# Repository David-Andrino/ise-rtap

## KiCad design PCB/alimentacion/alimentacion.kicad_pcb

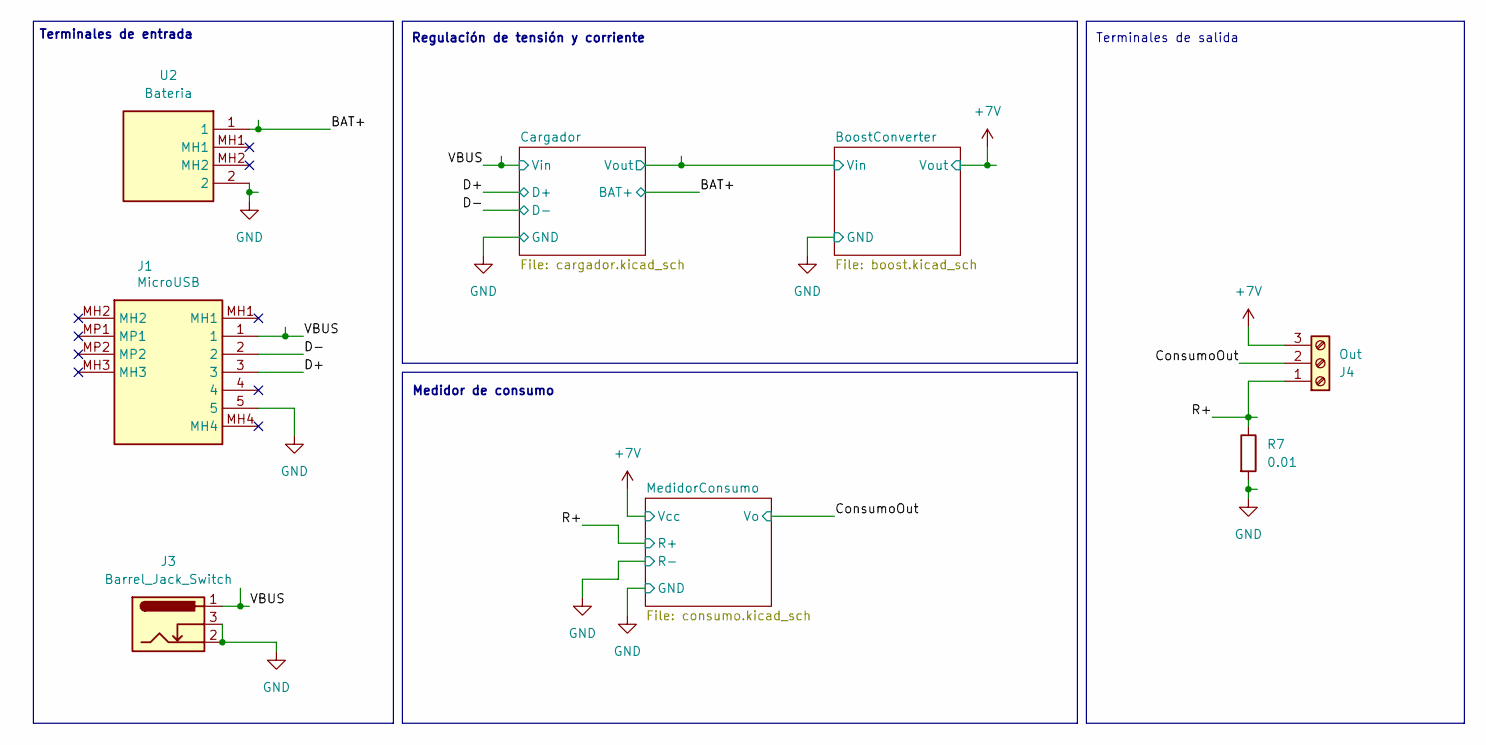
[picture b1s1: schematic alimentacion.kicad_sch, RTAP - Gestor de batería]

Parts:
J1: MicroUSB; 101181940001LF; Manufacturer_Part_Number 10118194-0001LF
J3: Barrel_Jack_Switch; PJ202AH
J4: Out; TerminalBlock_bornier-3_P5.08mm
R7: 0.01; R_1206_3216Metric
U2: Bateria; 12BHC186P1GR; Mouser Part Number 12BHC186P1-GR

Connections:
+7V: J4.3; also elsewhere on the board
/BAT+: U2.1; also elsewhere on the board
/ConsumoOut: J4.2; also elsewhere on the board
/D+: J1.3; also elsewhere on the board
/D-: J1.2; also elsewhere on the board
/R+: J4.1, R7.1; also elsewhere on the board
/VBUS: J1.1, J3.1; also elsewhere on the board
GND: J1.5, J3.2, J3.3, R7.2, U2.2; also elsewhere on the board

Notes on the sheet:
Terminales de salida
Medidor de consumo
Terminales de entrada
Regulación de tensión y corriente

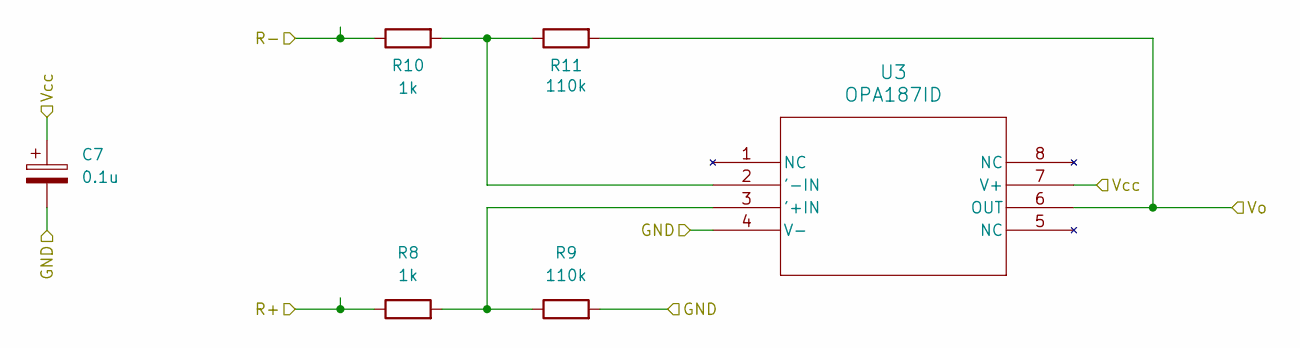
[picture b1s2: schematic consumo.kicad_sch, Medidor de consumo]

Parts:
C7: 0.1u; C_0603_1608Metric
R8, R10: 1k; R_0603_1608Metric
R9, R11: 110k; R_0603_1608Metric
U3: OPA187ID; D8_TEX-M

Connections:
+7V: C7.1, U3.7 (V+); also elsewhere on the board
/ConsumoOut: R11.2, U3.6 (OUT); also elsewhere on the board
/R+: R8.1; also elsewhere on the board
GND: C7.2, R9.2, R10.1, U3.4 (V-); also elsewhere on the board
unnamed: R8.2, R9.1, U3.3 ('+IN)
unnamed: R10.2, R11.1, U3.2 ('-IN)

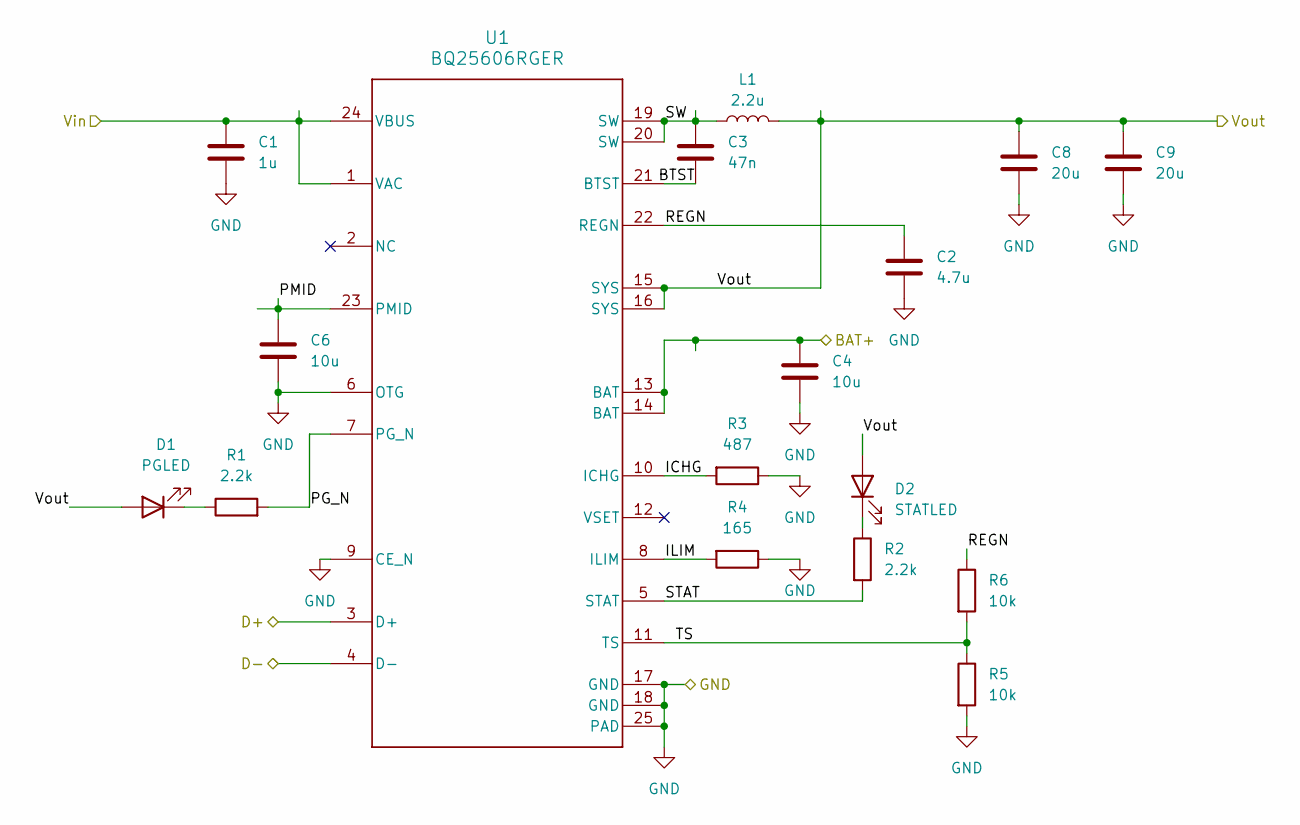
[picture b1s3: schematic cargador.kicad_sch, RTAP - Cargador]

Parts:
C1: 1u; C_0603_1608Metric
C2: 4.7u; C_0603_1608Metric
C3: 47n; C_0603_1608Metric
C4, C6: 10u; C_0603_1608Metric
C8, C9: 20u; C_0603_1608Metric
D1: PGLED; D_0603_1608Metric_Pad1.05x0.95mm_HandSolder
D2: STATLED; D_0603_1608Metric_Pad1.05x0.95mm_HandSolder
L1: 2.2u; SRN6045
R1, R2: 2.2k; R_0603_1608Metric
R3: 487; R_0603_1608Metric
R4: 165; R_0603_1608Metric
R5, R6: 10k; R_0603_1608Metric
U1: BQ25606RGER; RGE0024H_NV

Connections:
/BAT+: C4.2, U1.13 (BAT), U1.14 (BAT); also elsewhere on the board
/BoostConverter/Vin: C8.2, C9.2, D1.2 (A), D2.2 (A), L1.2, U1.15 (SYS), U1.16 (SYS); also elsewhere on the board
/Cargador/BTST: C3.2, U1.21 (BTST)
/Cargador/ICHG: R3.2, U1.10 (ICHG)
/Cargador/ILIM: R4.2, U1.8 (ILIM)
/Cargador/PG_N: R1.2, U1.7 (PG_N)
/Cargador/PMID: C6.1, U1.23 (PMID)
/Cargador/REGN: C2.2, R6.1, U1.22 (REGN)
/Cargador/STAT: R2.2, U1.5 (STAT)
/Cargador/SW: C3.1, L1.1, U1.19 (SW), U1.20 (SW)
/Cargador/TS: R5.1, R6.2, U1.11 (TS)
/D+: U1.3 (D+); also elsewhere on the board
/D-: U1.4 (D-); also elsewhere on the board
/VBUS: C1.1, U1.1 (VAC), U1.24 (VBUS); also elsewhere on the board
GND: C1.2, C2.1, C4.1, C6.2, C8.1, C9.1, R3.1, R4.1, R5.2, U1.6 (OTG), U1.9 (CE_N), U1.17 (GND), U1.18 (GND), U1.25 (PAD); also elsewhere on the board
unnamed: D1.1 (K), R1.1
unnamed: D2.1 (K), R2.1

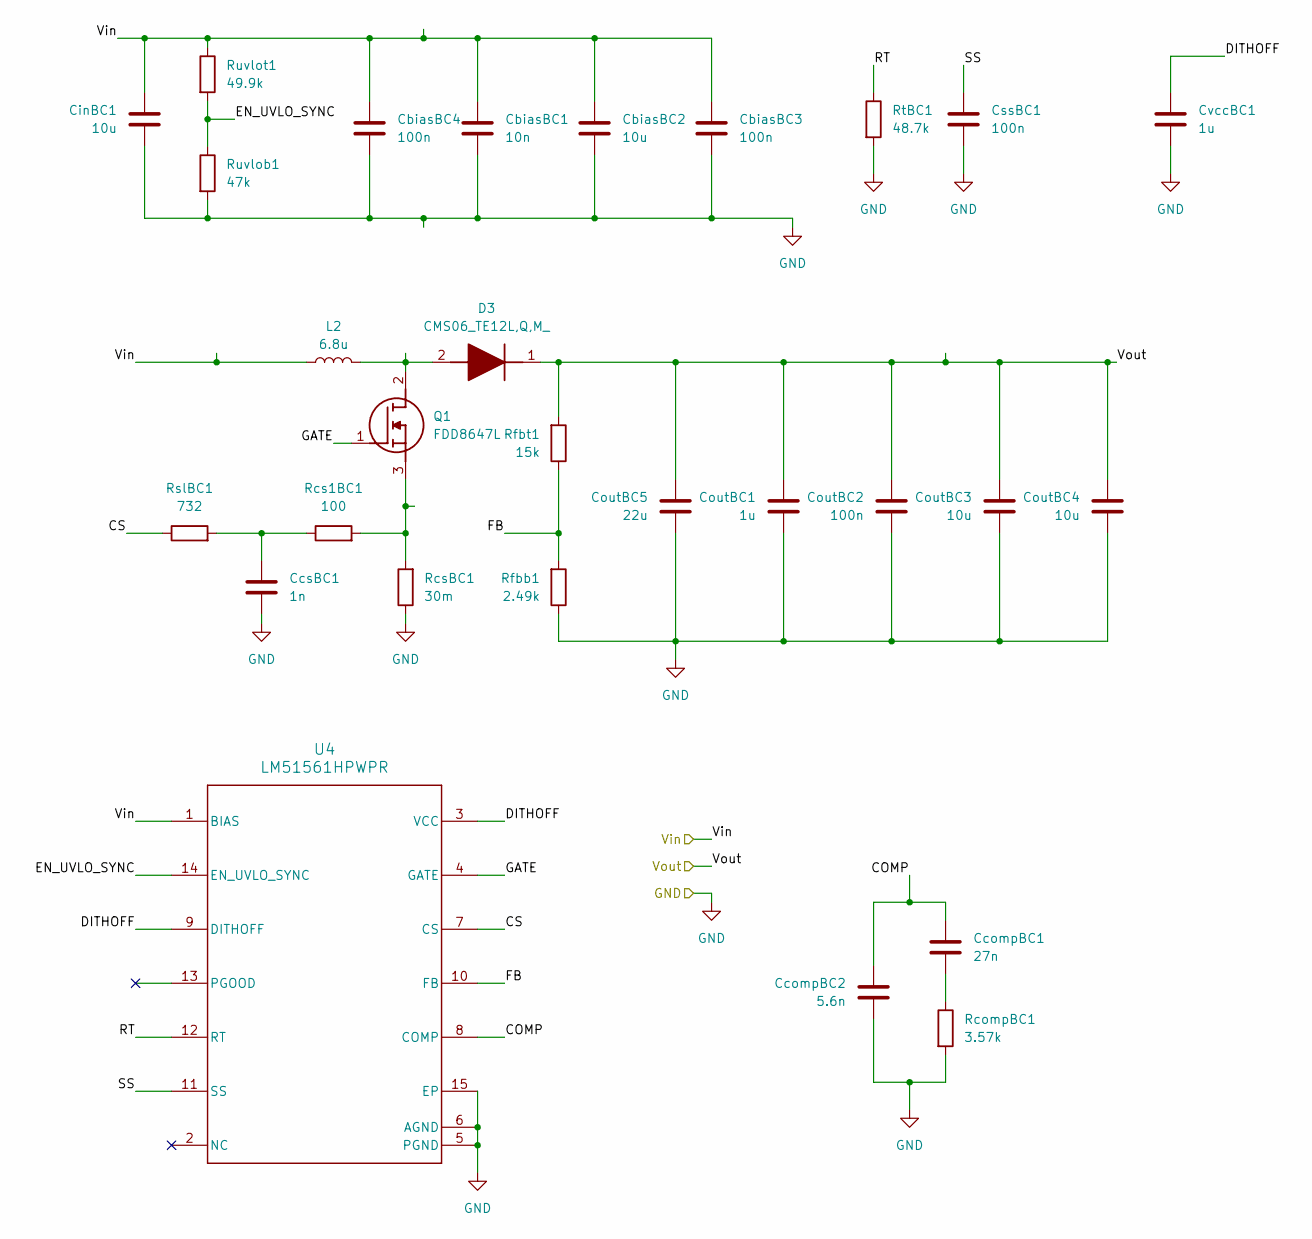
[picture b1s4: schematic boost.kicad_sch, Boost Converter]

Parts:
CbiasBC1: 10n; C_1206_3216Metric_Pad1.33x1.80mm_HandSolder
CbiasBC2: 10u; C_1206_3216Metric_Pad1.33x1.80mm_HandSolder
CbiasBC3, CbiasBC4: 100n; C_1206_3216Metric_Pad1.33x1.80mm_HandSolder
CcompBC1: 27n; C_0603_1608Metric
CcompBC2: 5.6n; C_0603_1608Metric
CcsBC1: 1n; C_0603_1608Metric
CinBC1: 10u; C_1206_3216Metric_Pad1.33x1.80mm_HandSolder
CoutBC1: 1u; C_1206_3216Metric_Pad1.33x1.80mm_HandSolder
CoutBC2: 100n; C_1206_3216Metric_Pad1.33x1.80mm_HandSolder
CoutBC3, CoutBC4: 10u; C_1206_3216Metric_Pad1.33x1.80mm_HandSolder
CoutBC5: 22u; C_1206_3216Metric_Pad1.33x1.80mm_HandSolder
CssBC1: 100n; C_0603_1608Metric
CvccBC1: 1u; C_0603_1608Metric
D3: CMS06_TE12L,Q,M_; SODFL4724X108N; Mouser Part Number 757-CMS06TE12L,Q,M
L2: 6.8u; SRN6045
Q1: FDD8647L; Mouser Part Number 512-FDD8647L
RcompBC1: 3.57k; R_0603_1608Metric
Rcs1BC1: 100; R_0603_1608Metric
RcsBC1: 30m; R_1206_3216Metric
Rfbb1: 2.49k; R_0603_1608Metric
Rfbt1: 15k; R_0603_1608Metric
RslBC1: 732; R_0603_1608Metric
RtBC1: 48.7k; R_0603_1608Metric
Ruvlob1: 47k; R_0603_1608Metric
Ruvlot1: 49.9k; R_0603_1608Metric
U4: LM51561HPWPR; PWP0014H-IPC_A

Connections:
+7V: CoutBC1.2, CoutBC2.2, CoutBC3.2, CoutBC4.2, CoutBC5.2, D3.1 (K), Rfbt1.2; also elsewhere on the board
/BoostConverter/COMP: CcompBC1.2, CcompBC2.2, U4.8 (COMP)
/BoostConverter/CS: RslBC1.1, U4.7 (CS)
/BoostConverter/DITHOFF: CvccBC1.2, U4.3 (VCC), U4.9 (DITHOFF)
/BoostConverter/EN_UVLO_SYNC: Ruvlob1.1, Ruvlot1.2, U4.14 (EN_UVLO_SYNC)
/BoostConverter/FB: Rfbb1.2, Rfbt1.1, U4.10 (FB)
/BoostConverter/GATE: Q1.1 (G), U4.4 (GATE)
/BoostConverter/RT: RtBC1.1, U4.12 (RT)
/BoostConverter/SS: CssBC1.2, U4.11 (SS)
/BoostConverter/Vin: CbiasBC1.2, CbiasBC2.2, CbiasBC3.2, CbiasBC4.2, CinBC1.1, L2.1, Ruvlot1.1, U4.1 (BIAS); also elsewhere on the board
GND: CbiasBC1.1, CbiasBC2.1, CbiasBC3.1, CbiasBC4.1, CcompBC2.1, CcsBC1.1, CinBC1.2, CoutBC1.1, CoutBC2.1, CoutBC3.1, CoutBC4.1, CoutBC5.1, CssBC1.1, CvccBC1.1, RcompBC1.2, RcsBC1.1, Rfbb1.1, RtBC1.2, Ruvlob1.2, U4.5 (PGND), U4.6 (AGND), U4.15 (EP); also elsewhere on the board
unnamed: CcompBC1.1, RcompBC1.1
unnamed: CcsBC1.2, Rcs1BC1.1, RslBC1.2
unnamed: D3.2 (A), L2.2, Q1.2 (D)
unnamed: Q1.3 (S), Rcs1BC1.2, RcsBC1.2

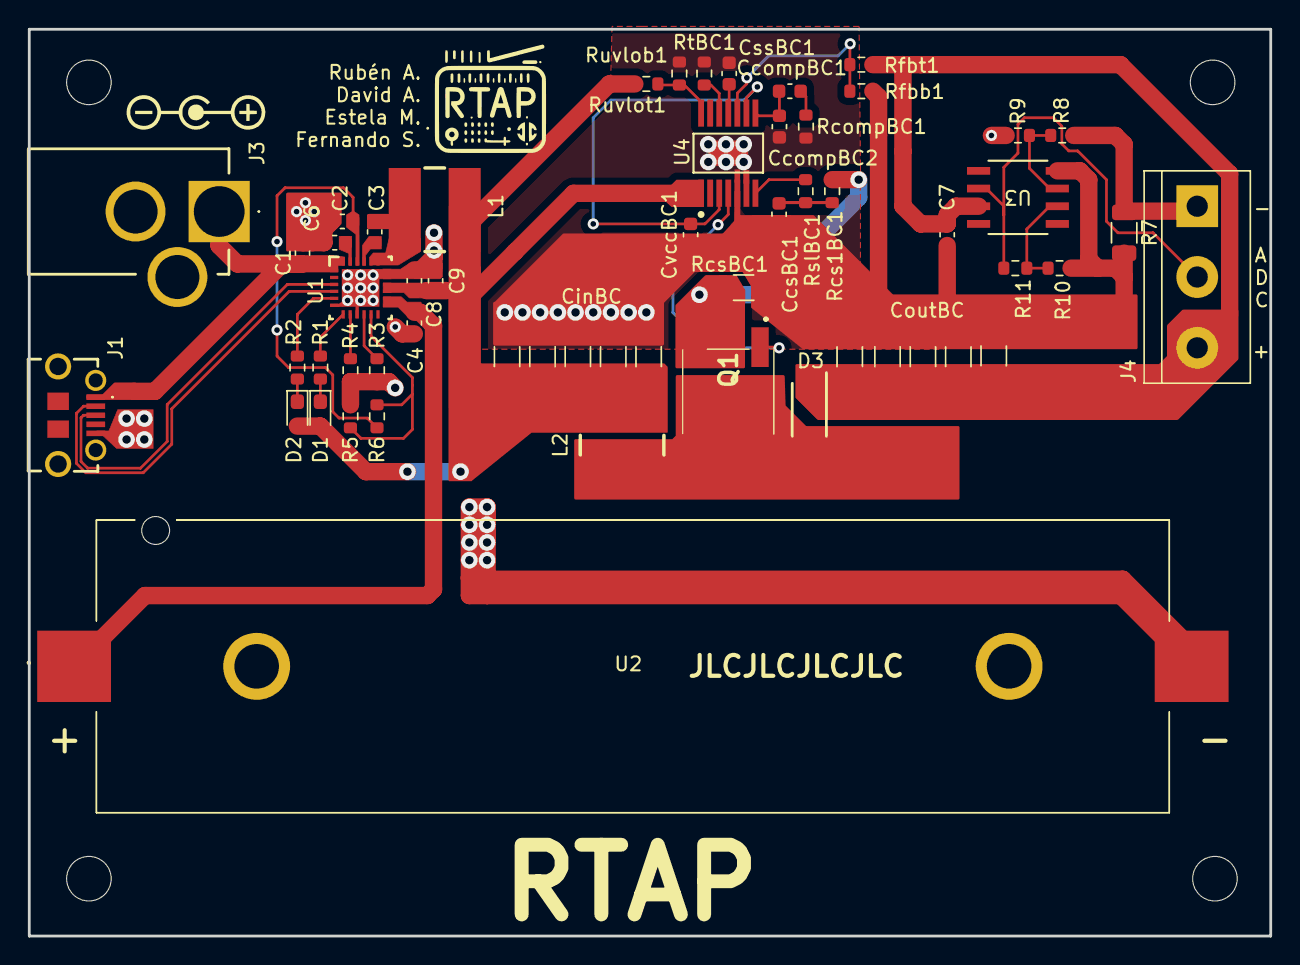
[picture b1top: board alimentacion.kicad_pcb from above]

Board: 2 copper layers, 89.1 x 65.1 mm, 56 parts (0 on the bottom side), 34 nets.

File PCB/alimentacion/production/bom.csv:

Designator,Footprint,Quantity,Value,LCSC Part #
"C1, CvccBC1",0603,2,1u,
C2,0603,1,4.7u,
C3,0603,1,47n,
"C4, C6",0603,2,10u,
C7,0603,1,0.1u,
"C8, C9",0603,2,20u,
CbiasBC1,1206,1,10n,
"CbiasBC2, CinBC1, CoutBC3, CoutBC4",1206,4,10u,
"CbiasBC3, CbiasBC4, CoutBC2",1206,3,100n,
CcompBC1,0603,1,27n,
CcompBC2,0603,1,5.6n,
CcsBC1,0603,1,1n,
CoutBC1,1206,1,1u,
CoutBC5,1206,1,22u,
CssBC1,0603,1,100n,
D1,0603,1,PGLED,
D2,0603,1,STATLED,
D3,SODFL4724X108N,1,"CMS06_TE12L,Q,M_",
J1,101181940001LF,1,MicroUSB,
J3,PJ202AH,1,Barrel_Jack_Switch,
J4,TerminalBlock_bornier-3_P5.08mm,1,Out,
L1,SRN6045,1,2.2u,
L2,SRN6045,1,6.8u,
Q1,FDD8647L,1,FDD8647L,
"R1, R2",0603,2,2.2k,
"R10, R8",0603,2,1k,
"R11, R9",0603,2,110k,
R3,0603,1,487,
R4,0603,1,165,
"R5, R6",0603,2,10k,
R7,1206,1,0.01,
RcompBC1,0603,1,3.57k,
Rcs1BC1,0603,1,100,
RcsBC1,1206,1,30m,
Rfbb1,0603,1,2.49k,
Rfbt1,0603,1,15k,
RslBC1,0603,1,732,
RtBC1,0603,1,48.7k,
Ruvlob1,0603,1,47k,
Ruvlot1,0603,1,49.9k,
U1,RGE0024H_NV,1,BQ25606RGER,
U2,12BHC186P1GR,1,Bateria,
U3,D8_TEX-M,1,OPA187ID,
U4,PWP0014H-IPC_A,1,LM51561HPWPR,

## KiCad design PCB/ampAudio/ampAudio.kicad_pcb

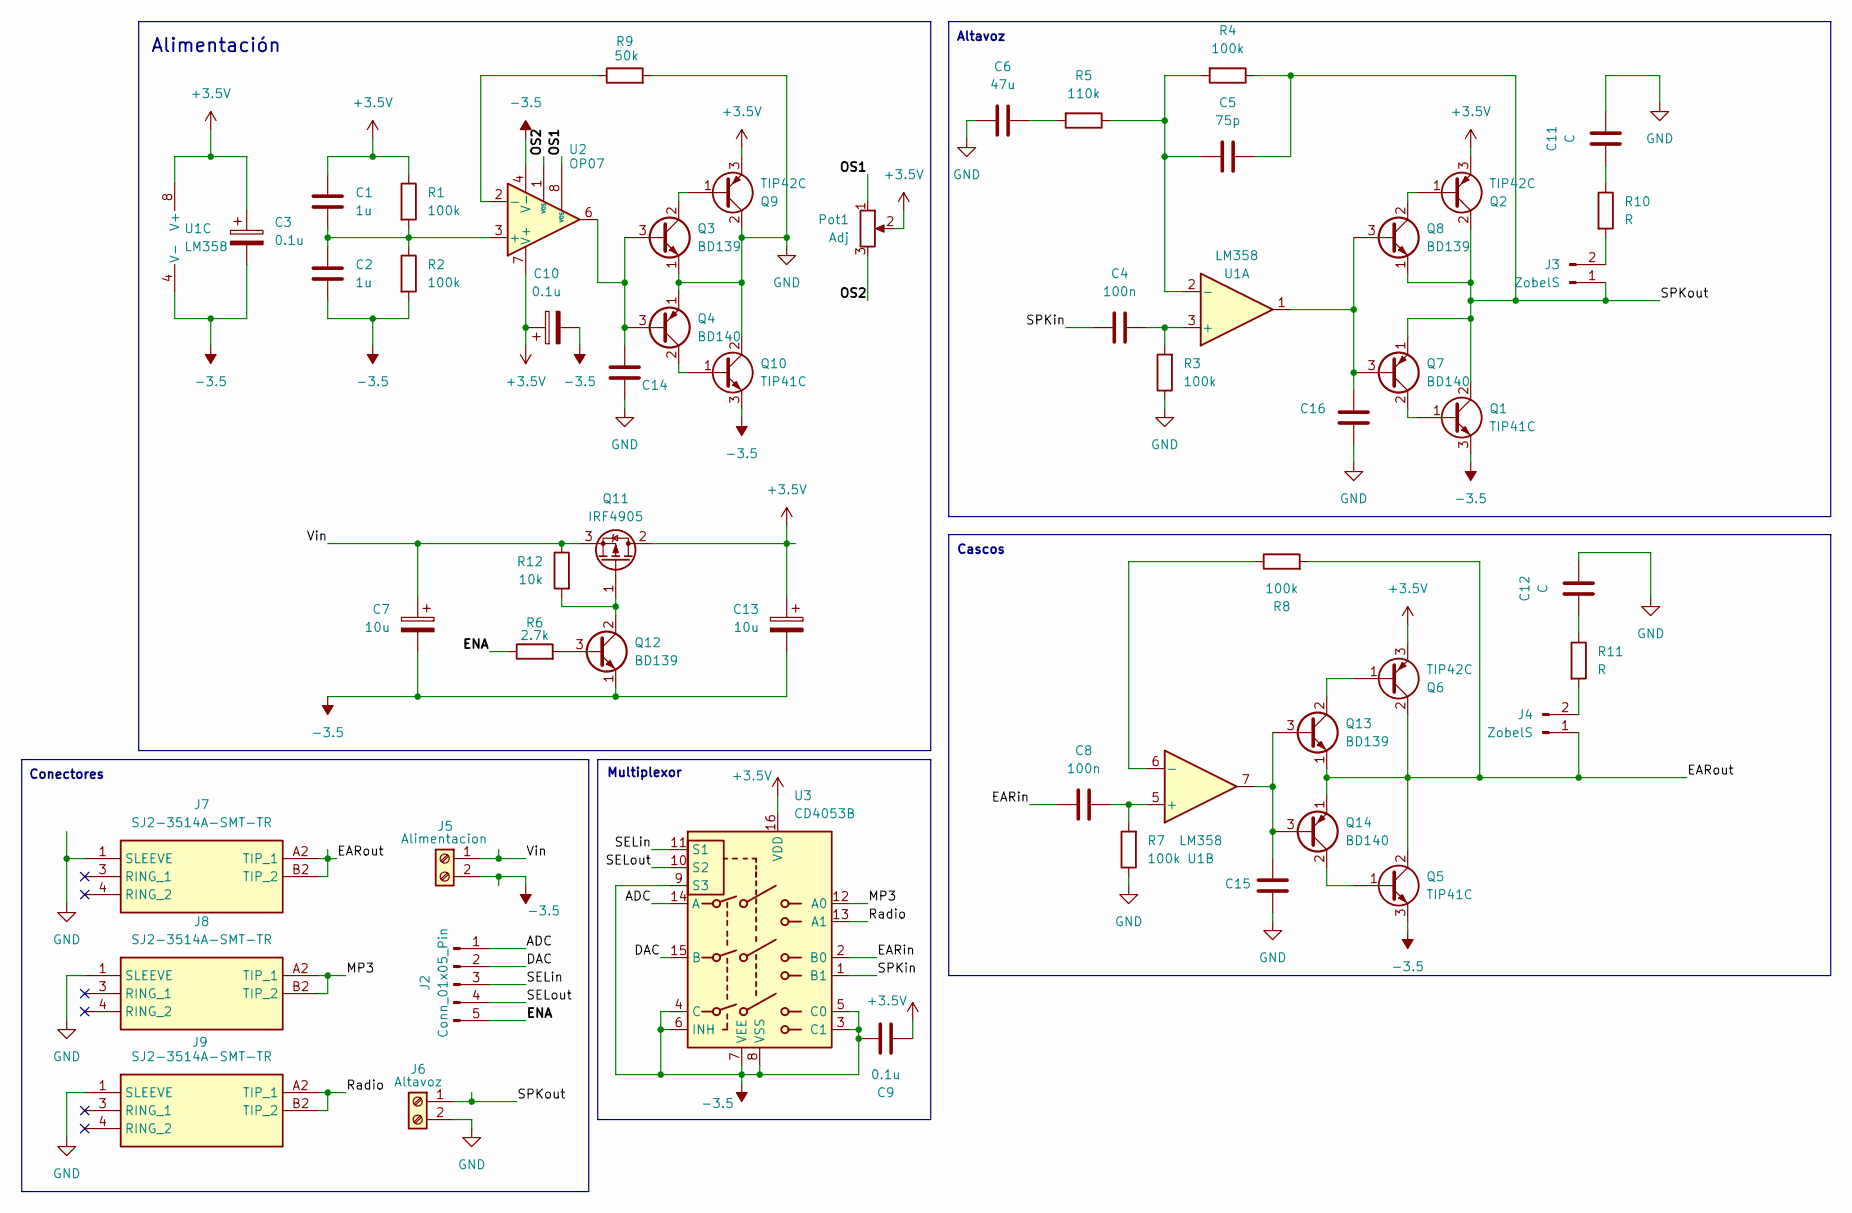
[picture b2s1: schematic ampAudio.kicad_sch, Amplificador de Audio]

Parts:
C1, C2, C14, C15, C16: 1u; C_1206_3216Metric
C3, C9, C10: 0.1u; C_1206_3216Metric
C4, C8: 100n; C_1206_3216Metric
C5: 75p; C_1206_3216Metric
C6: 47u; C_1206_3216Metric
C7, C13: 10u; C_1206_3216Metric
C11, C12: C; C_1206_3216Metric
J2: Conn_01x05_Pin; PinHeader_1x05_P2.54mm_Vertical
J3, J4: ZobelS; PinHeader_1x02_P2.54mm_Vertical
J5: Alimentacion; TerminalBlock_bornier-2_P5.08mm
J6: Altavoz; TerminalBlock_bornier-2_P5.08mm
J7, J8, J9: SJ2-3514A-SMT-TR; SJ23514ASMTTR; Mouser Part Number 490-SJ2-3514A-SMT-TR
Pot1: Adj; Potentiometer_Piher_PT-10-V10_Vertical
Q1, Q5, Q10: TIP41C; TO-220-3_Vertical
Q2, Q6, Q9: TIP42C; TO-220-3_Vertical
Q3, Q8, Q12, Q13: BD139; TO-126-3_Vertical
Q4, Q7, Q14: BD140; TO-126-3_Vertical
Q11: IRF4905; TO-220-3_Vertical
R1, R2, R3, R4, R7, R8: 100k; R_1206_3216Metric
R5: 110k; R_1206_3216Metric
R6: 2.7k; R_1206_3216Metric
R9: 50k; R_1206_3216Metric
R10, R11: R; R_1206_3216Metric
R12: 10k; R_1206_3216Metric
U1: LM358; DIP-8_W7.62mm_Socket_LongPads
U2: OP07; DIP-8_W7.62mm_Socket_LongPads
U3: CD4053B; DIP-16_W7.62mm_Socket_LongPads

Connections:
+3.5V: C1.1, C3.1, C9.1, C10.1, C13.1, Pot1.2, Q2.3 (E), Q6.3 (E), Q9.3 (E), Q11.2 (D), R1.1, U1.8 (V+), U2.7 (V+), U3.16 (VDD)
-3.5: C2.2, C3.2, C7.2, C9.2, C10.2, C13.2, J5.2, Q1.3 (E), Q5.3 (E), Q10.3 (E), Q12.1 (E), R2.2, U1.4 (V-), U2.4 (V-), U3.3 (C1), U3.4 (C), U3.5 (C0), U3.6 (INH), U3.7 (VEE), U3.8 (VSS), U3.9 (S3)
/ADC: J2.1, U3.14 (A)
/DAC: J2.2, U3.15 (B)
/EARin: C8.1, U3.2 (B0)
/EARout: J4.1, J7.A2 (TIP_1), J7.B2 (TIP_2), Q5.2 (C), Q6.2 (C), Q13.1 (E), Q14.1 (E), R8.2
/ENA: J2.5, R6.1
/MP3: J8.A2 (TIP_1), J8.B2 (TIP_2), U3.12 (A0)
/OS1: Pot1.1, U2.8 (VOS)
/OS2: Pot1.3, U2.1 (VOS)
/Radio: J9.A2 (TIP_1), J9.B2 (TIP_2), U3.13 (A1)
/SELin: J2.3, U3.11 (S1)
/SELout: J2.4, U3.10 (S2)
/SPKin: C4.1, U3.1 (B1)
/SPKout: C5.2, J3.1, J6.1, Q1.2 (C), Q2.2 (C), Q7.1 (E), Q8.1 (E), R4.1
/Vin: C7.1, J5.1, Q11.3 (S), R12.1
GND: C6.1, C11.2, C12.2, C14.2, C15.2, C16.2, J6.2, J7.1 (SLEEVE), J8.1 (SLEEVE), J9.1 (SLEEVE), Q3.1 (E), Q4.1 (E), Q9.2 (C), Q10.2 (C), R3.1, R7.1, R9.2
unnamed: C6.2, R5.2
unnamed: C11.1, R10.1
unnamed: C12.1, R11.1
unnamed: J3.2, R10.2
unnamed: J4.2, R11.2
unnamed: Q1.1 (B), Q7.2 (C)
unnamed: Q2.1 (B), Q8.2 (C)
unnamed: C14.1, Q3.3 (B), Q4.3 (B), U2.6
unnamed: Q3.2 (C), Q9.1 (B)
unnamed: C16.1, Q7.3 (B), Q8.3 (B), U1.1
unnamed: Q4.2 (C), Q10.1 (B)
unnamed: Q11.1 (G), Q12.2 (C), R12.2
unnamed: Q12.3 (B), R6.2
unnamed: C15.1, Q13.3 (B), Q14.3 (B), U1.7
unnamed: Q6.1 (B), Q13.2 (C)
unnamed: Q5.1 (B), Q14.2 (C)
unnamed: C4.2, R3.2, U1.3 (+)
unnamed: C5.1, R4.2, R5.1, U1.2 (-)
unnamed: C8.2, R7.2, U1.5 (+)
unnamed: R8.1, U1.6 (-)
unnamed: C1.2, C2.1, R1.2, R2.1, U2.3 (+)
unnamed: R9.1, U2.2 (-)

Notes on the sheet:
Alimentación
Altavoz
Conectores
Cascos
Multiplexor

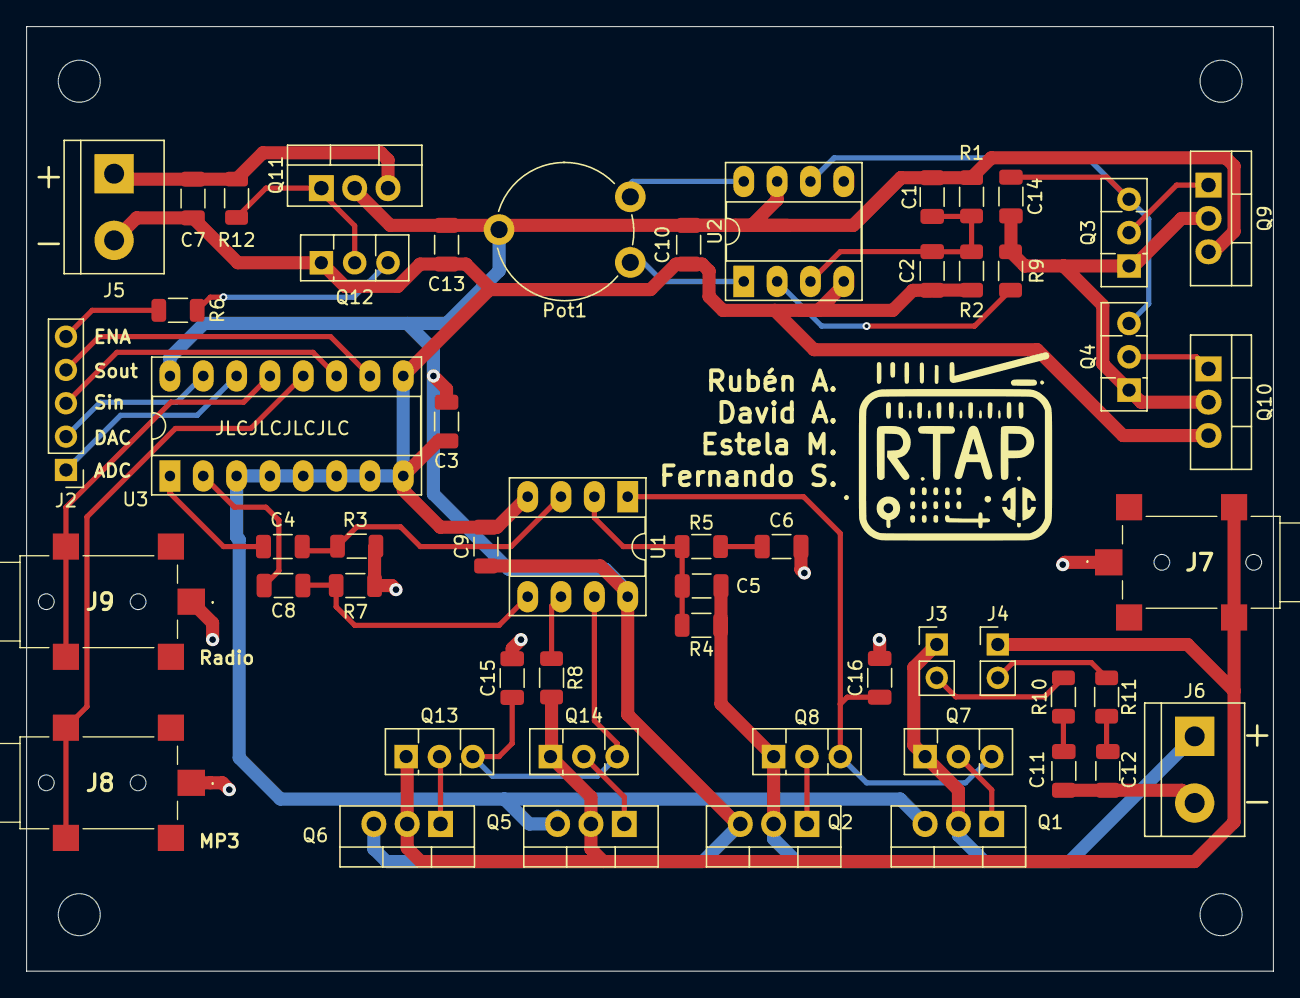
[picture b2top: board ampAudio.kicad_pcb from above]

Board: 2 copper layers, 95.0 x 72.0 mm, 54 parts (0 on the bottom side), 39 nets.

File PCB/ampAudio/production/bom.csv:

Designator,Footprint,Quantity,Value,LCSC Part #
"C1, C14, C15, C16, C2",1206,5,1u,
"C10, C3, C9",1206,3,0.1u,
"C11, C12",1206,2,C,
"C13, C7",1206,2,10u,
"C4, C8",1206,2,100n,
C5,1206,1,75p,
C6,1206,1,47u,
J2,PinHeader_1x05_P2.54mm_Vertical,1,Conn_01x05_Pin,
"J3, J4",PinHeader_1x02_P2.54mm_Vertical,2,ZobelS,
J5,TerminalBlock_bornier-2_P5.08mm,1,Alimentacion,
J6,TerminalBlock_bornier-2_P5.08mm,1,Altavoz,
"J7, J8, J9",SJ23514ASMTTR,3,SJ2-3514A-SMT-TR,
Pot1,Potentiometer_Piher_PT-10-V10_Vertical,1,Adj,
"Q1, Q10, Q5",TO-220-3_Vertical,3,TIP41C,
Q11,TO-220-3_Vertical,1,IRF4905,
"Q12, Q13, Q3, Q8",TO-126-3_Vertical,4,BD139,
"Q14, Q4, Q7",TO-126-3_Vertical,3,BD140,
"Q2, Q6, Q9",TO-220-3_Vertical,3,TIP42C,
"R1, R2, R3, R4, R7, R8",1206,6,100k,
"R10, R11",1206,2,R,
R12,1206,1,10k,
R5,1206,1,110k,
R6,1206,1,2.7k,
R9,1206,1,50k,
U1,DIP-8_W7.62mm_Socket_LongPads,1,LM358,
U2,DIP-8_W7.62mm_Socket_LongPads,1,OP07,
U3,DIP-16_W7.62mm_Socket_LongPads,1,CD4053B,

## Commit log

2024-04-11 Añadir Radio y MP3 al proyecto
2024-04-15 Finalizar los test modulares
2024-04-16 Crear .gitignore
2024-04-21 ADC-DMA basic functionallity
2024-04-21 Create ADC test and modularize library
2024-04-21 Crear modulo y test de ADC (#7)
2024-04-21 Move signal generation out of adc file
2024-04-22 Crear la interfaz de la página web
2024-04-22 Arreglar modulo del timer y añadir fflush en el test
2024-04-22 Create F7 adaptation of ADC
2024-04-22 Create DAC-DMA project, implementation and tests
2024-04-23 Terminar interfaz de la página web
2024-04-23 Adapt adc to F7
2024-04-23 Actualizar web
2024-04-23 Añadir botón para enviar canción
2024-04-23 Adapt DAC for Cortex F7
2024-04-23 Move tests to test-dac files
2024-04-26 Crear proyecto nfc
2024-04-27 Create .clang-format and Makefile to run it
2024-04-27 Crear proyecto de dsp
2024-04-27 Create audioPath project
2024-04-27 Create LPF audio tunnel test
2024-04-27 Fix test frequency to 1kHz and yprev start size
2024-04-27 Parametrizar ficheros de audio
2024-04-27 Parametrizar el resto de ficheros
2024-04-27 Fix ADC trigger const
2024-04-27 Apply formatting
2024-04-28 Interfaz
2024-04-28 Bajo nivel del procesador de señal
2024-04-28 Cambiar .clang-format para que alinee macros y no tenga maximo de ancho
2024-04-28 Añadir saturación y test con botón
2024-04-28 Añadir documentación a módulo DSP
2024-04-29 Update layout
2024-04-30 Radio
2024-04-30 Terminar la página web
2024-04-30 Todo menos mp3
2024-05-02 Adaptar página web a STM32F7
2024-05-02 portacion
2024-05-02 Añadir RTC a la página web
2024-05-02 Añadir el thread que recibe los msg del main
2024-05-02 Interrupciones b1, planteamiento modos bajo consumo
2024-05-02 Añadir modulos a mainModule (algunos solo el header)
2024-05-02 Define message format
2024-05-02 Eliminar ctrl_out_thread
2024-05-02 Crear controlConfig.h y switches para procesamiento de mensajes
2024-05-02 Actualizar el módulo de DSP a la última versión
2024-05-02 Añadir otros módulos intento 2
2024-05-02 Eliminar test de DSP e importar módulos de ADC, DAC y DMA
2024-05-02 Añadir respuestas a todas las acciones de momento y crear colas en headers
2024-05-02 Añadir mensajes de llegada de la radio
2024-05-03 Actualizar tiempo y consumo en tiempo real
2024-05-03 Adaptar Radio y Página Web al programa principal
2024-05-03 Quitar autenticación
2024-05-03 Add consumption sampling
2024-05-03 Limpiar proyecto raiz
2024-05-03 Aplicar formato
2024-05-03 Crear Doxyfile
2024-05-03 Modo StandBy funcionando
2024-05-04 Arreglar la actualización del consumo y la fecha de forma simultánea
2024-05-04 Añadir ficheros de la WEB
2024-05-04 Añadir archivo de texto con cambios para adapatar la Web
2024-05-04 Poner nombre a la cola del control
2024-05-04 Cambiar UART del MP3
2024-05-04 Cambiar I2C de la radio
2024-05-04 Añadir inicialización de radio y mp3 al principio del control
2024-05-04 Arreglar desplazamiento de fecha y hora
2024-05-04 Adaptar RTC al proyecto
2024-05-04 Apagar la radio y el MP3 en el modo bajo consumo
2024-05-04 Eliminar esperas activas en la radio
2024-05-04 Añadir documentacion a la radio, MP3 y a la web
2024-05-04 Arreglar medición periódica de consumo
2024-05-04 Todo el NFC :)
2024-05-04 NFC con PullUp en GPO
2024-05-04 Disable NoPull
2024-05-04 Aplicar cambios para integrar la web y el rtc
2024-05-04 Añadir mensaje de contestación de la radio a un seek
2024-05-04 Enviar consumo a la pantalla también
2024-05-04 Enviar frecuencia al cambiar con el NFC
2024-05-04 numSongs
2024-05-04 NFC y uSD comentados
2024-05-04 Crear modulo de i2c
2024-05-04 Limpiar restos de I2C en radio.c
2024-05-04 Los botones conservan estado. Redefinicion de callbacks
2024-05-04 Minor changes
2024-05-04 Logo RTAP codigo
2024-05-04 Arreglar lista canciones
2024-05-04 Solucionar error en el indice de las canciones
2024-05-04 Añadir NFC, uSD y FatFs
2024-05-04 Quitar suma al indice de las canciones
2024-05-04 Arreglar indices canciones y funcion de buscar cancion
2024-05-04 Quitar pines del boton en el RTC
2024-05-05 Arreglar signo de las bandas en la web
2024-05-05 Eliminar tests de ADC y Web
2024-05-05 Arreglar comentarios radio.h
2024-05-05 Arreglar comentarios adc.h
2024-05-05 Comentar i2c.h
2024-05-05 Documentar controlConfig.h
2024-05-05 Documentar controlThread.h
2024-05-05 Eliminar ficheros de test del DAC
2024-05-05 Documentar audioConfig.h
2024-05-05 Crear grupo de I2C
2024-05-05 Documentar módulos de DSP
2024-05-05 Añadir nombres de los ficheros y arreglos menores
2024-05-06 Adaptar LCD
2024-05-06 Añadir encendido y apagado de amplificador en arranque y bajo consumo
2024-05-06 NFC adaptado
2024-05-06 Documentar MP3 y Web
2024-05-06 Cambiar valores primera banda
2024-05-06 Documentar Radio
2024-05-06 Separar los forms de la entrada
2024-05-06 Arreglar el RTC
2024-05-06 Definir callbacks en gui.c
2024-05-06 Cambiar delay de muestreo de consumo
2024-05-06 Sumar uno al indice de la cancion en el lcd
2024-05-06 Cambiar cola de entrada al dspThread. Ahora interpreta todos los mensajes en lugar de solo el último.
2024-05-07 Añadir pullup al GPO del NFC
2024-05-07 Redefinicion callback de los controles del MP3
2024-05-07 Callbacks radio
2024-05-07 Cambio cola radio a ctrl_in_queue
2024-05-07 variables definidas como volatiles para que el compilador no optimice
2024-05-07 Configuracion proyecto
2024-05-08 Cambios en el manejo del volumen
2024-05-08 Escala del volumen
2024-05-08 Resueltos pequeños fallos en el volumen
2024-05-08 Crear configuracion de devcontainer e importar plantilla de la introduccion
2024-05-09 Habemus sd
2024-05-09 Crear estructura y primer fichero
2024-05-09 Eliminar carpeta out y añadir a .gitignore
2024-05-09 Badabin badabun
2024-05-09 Leer configuración en el arranque
2024-05-09 Cambiar fondo de escala del consumo
2024-05-09 Intento de guardar en la SD
2024-05-09 Cambiar llamada a modo de bajo consumo
2024-05-09 Añadir comprobación de errores al arrancar hilos y ErrorHandler
2024-05-10 Nueva funcionalidad: Añadido boton de restablecer filtros
2024-05-10 Restablecidos tamaños de threads y mutex
2024-05-10 Cambios en la funcionalidad del looping
2024-05-10 Cambiar estado inicial de la pantalla
2024-05-10 Cambiar frecuencias centrales de DSP
2024-05-10 Iniciar NFC
2024-05-10 Cambios prioridad threads
2024-05-11 Crear estructura de carpetas y algunos ficheros
2024-05-11 Terminar la estructura del fichero
2024-05-11 Memoria del circuito de carga
2024-05-11 Librerias
2024-05-11 Terminar circuito de alimentacion
2024-05-11 Añadir MP3 y Radio a la memoria
2024-05-11 Completar Radio y MP3
2024-05-11 Corregir alimentacion, circuito de audio y problema de tierras
2024-05-11 Interfaz tactil
2024-05-11 apartado de otras consideraciones
2024-05-12 Alimentar placa
2024-05-12 Añadir parte de la Web y modificar MP3, Radio y RTC
2024-05-12 nada
2024-05-12 Control, consumo y i2c
2024-05-12 Timer de adquisicion y control
2024-05-12 Cambios en la configuracion de los valores por defecto para la radio y el mp3
2024-05-12 Ligeros cambios de estilo. Cambio "Home" por "Inicio" y añado un espacio al boton de restablecer filtros
2024-05-12 Cambios en los comentarios para que sean acordes a la configuración. No hay cambios funcionales
2024-05-12 Valor inicial a web_cnt_canciones
2024-05-12 Cambio DSP_TIM_PERIOD de 174 a 224
2024-05-12 Cambios en las etiquetas de los filtros para que sean acordes con la web
2024-05-12 Fotos interfaz tactil
2024-05-12 Separacion en subsecciones. Desarrollo del bajo nivel
2024-05-12 Documentación del DSP
2024-05-12 Completar RTC, Radio y MP3. Terminar interfaz usuario web. Añadir test de RTC, Radio, MP3 y servidor web
2024-05-12 Test hardware
2024-05-13 Terminar todas mis partes
2024-05-13 Depuracion software
2024-05-13 Cambio el tamaño de highStageHandlers de 2 a 3
2024-05-13 Limpiar basura
2024-05-13 uSD actualizada
2024-05-13 Arreglar imagenes
2024-05-13 Añadido labels y referencias
2024-05-13 Crear presupuesto
2024-05-13 Limpiar la mierda x2
2024-05-13 Trabajo en equipo
2024-05-13 Adaptar la parte de estela
2024-05-13 Modulo SD
2024-05-13 Sobre la placa
2024-05-13 Arreglar estructura de ficheros
2024-05-13 Arreglar errores
2024-05-13 Juntar pantalla
2024-05-13 Mover fotos
2024-05-13 Corregir centering
2024-05-13 Crear apartado 1.2
2024-05-13 Arreglar ficheros
2024-05-13 Tft y touchpad
2024-05-13 Limpiar carpetas
2024-05-13 Añadir circuito analógico
2024-05-15 Fix timer prescaler
2024-05-15 Comentar frecuencia del TIM2
2024-05-21 Comentarios
2024-05-22 Añadir memoria compilada
2024-05-26 Arreglar la memoria
